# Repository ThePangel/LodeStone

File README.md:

# LodeStone

Don't lose your friends with this GPS LoRa P2P compass!

---

## The Idea 

### Where it came from
Just recently my district's fair started, and between all the crowds and the size of the fairgrounds It's pretty hard to find my friends, especially when we get separated, so with that and me playing a bunch of Minecraft this idea of a Mesh LoRa P2P compass came about.

The name is a reference to the lodestone block in Minecraft which lets you set custom compass targets.

---

### Features

- [ ] Compass like display pointing at the other nodes in the mesh network
- [ ] Top down map-like view of all nodes in the network
- [ ] Encrypted location data 
- [ ] Gesture based navigation using the gyroscope and accelerometer
- [ ] Short messages (Using some sort of keyboard using the gestures, or morse code)
- [ ] Heavily optimized battery life

---

### How would it work?
The device consists of 7 components:
- Seeed Studio XIAO ESP32 S3 Plus (As the brains of the device)
- Seeed Studio Lora32 SX1262 (For LoRa)
- Seeed Studio L76K GNSS Module (For GPS)
- GY-9250 BMP085 Module (For Accelerometer, Gyroscope and an actual compass)
- GC9A01 Round TFT screen 
- 503040 600mAh Battery
- Flexible antenna for the gps module (The standard ceramic one that comes with the module is far too bulky)

#### Connectivity 

The idea is that each node connects to each other individually or in groups, working simultaneously.

Pairing is done by a gesture password consisting of holds and taps, basically a morse code pin. You pair your devices using the same pin, then they handshake, share keys, and establish a connection.

Even if they are not paired (and if enabled), nodes retransmit incoming data packets to other users in the network to increase range.

#### Display 

The compass and map are drawn by taking GPS data from both nodes and the GY-9250 compass and accelerometer to calculate the direction the other node is at.

#### Battery

To optimize battery life and not saturate the airwaves, my system uses a Supply-demand approach. When the node (as a pendant or in the pocket) is still and facing away from the user, it is just listening for either location packets or a request packet. If it receives a location packet, it will update that node's location in memory and nothing else. If it receives a request packet, it will send its own location.

When the node is pulled up to be viewed, it will send a request packet to other nodes to update their location in memory, and a location packet so other nodes update it's location. It will do this at customizable intervals of time while it is being viewed. For signal integrity, the sending node must receive a confirmation packet back to ensure the transmission was successful. This workflow keeps battery usage to a minimum.

I still think it should ping at a set interval to guarante some type of connection, since maybe I can recieve my friends location, but he can't recieve my request so I knever know were he is
this could be also tied to speed using the accelerometer, this meaning, the more they move the more they send, if they are still it will default to some configurable interval

We could also tune transmition gain baised on distance, with some headroom of course

#### Interface

To maintain a compact formfactor, interaction with the node will be based on gestures, using the GY-9250 accelerometer and gyro.

Some of this gestures could be:
-   Tap/Double Tap
-   Shake
-   Tilt right/left/up/down

The menus would be similar to a smart watch.

#### Messaging

We can leverage our LoRa connection to send quick preconfigurable messages or write one at that moment using a gesture keyboard or morse code.

In the future I may develop an app to make this easier (tbh just use meshtashtic or meshcore atp), but this is intended for short notification like messages.

I would also like to add an SOS function that sends a signal to all nodes paired, or even if enabled on both ends, all nodes in the network, this will make the nodes flash red and highlight the SOS'ing node.

#### PCB 

The PCB is a simple 4 layer PCB that as compactly as possible houses all of the off the shelf components, making it very cheap and easy to assemble, the two outter planes hold traces and GND while the two inner layers are full ground pours, a bunch of vias connect the 4 GNDs to improve RF performance

#### 3D printed case

I will make a 3D printed case, as small and tight as possible for it to be portable and comfortable, of course anyone could design their own cases.

#### FOSS and modularity

I would like this project to be modular and community focused, so I encourage colaboration integrating for example:
-   Other ESP or microcontroller models
-   Other screens
-   Extra input components
-   Other IMU

etc.. all from the same modular firmware.

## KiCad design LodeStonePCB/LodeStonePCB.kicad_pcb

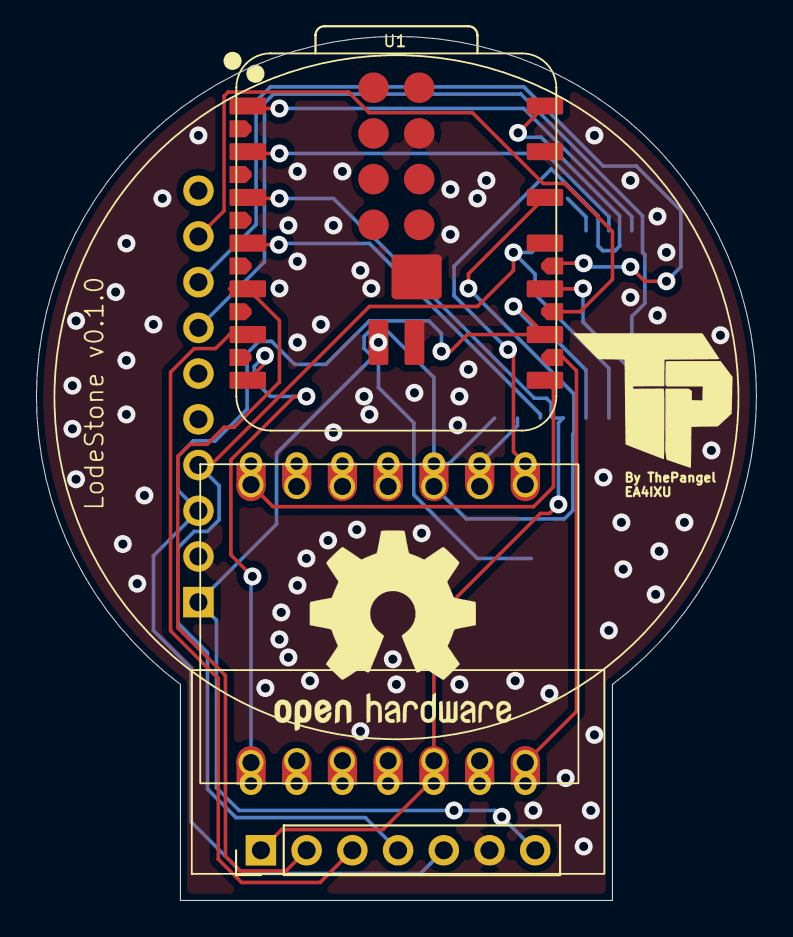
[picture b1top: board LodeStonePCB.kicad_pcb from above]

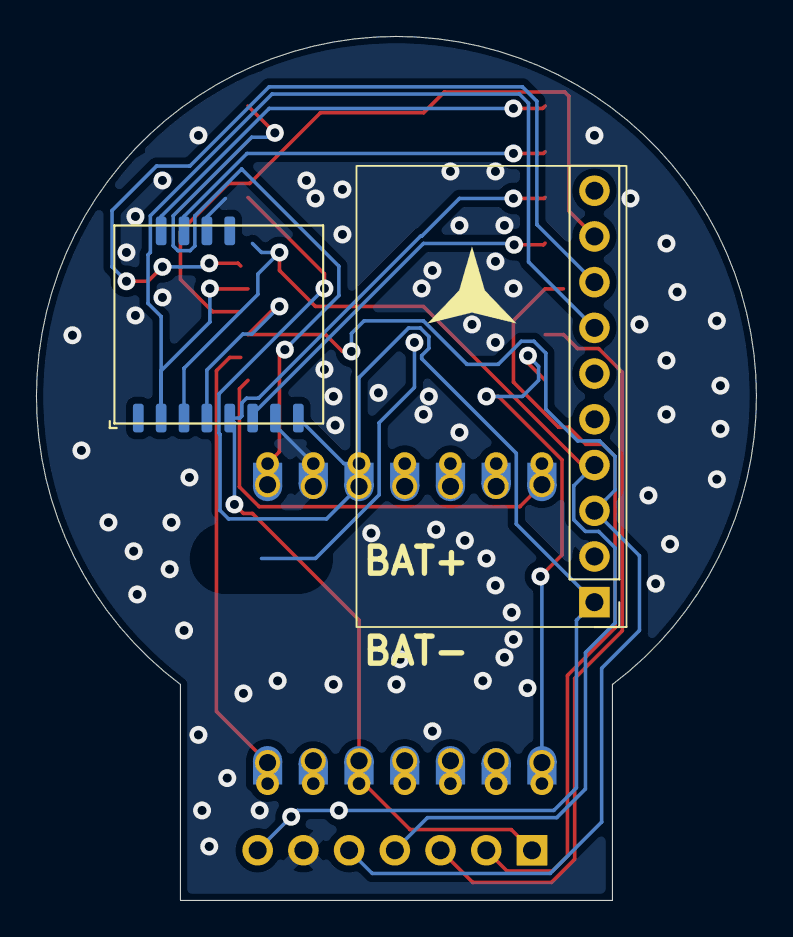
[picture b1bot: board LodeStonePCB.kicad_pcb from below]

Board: 4 copper layers, 40.0 x 48.0 mm, 5 parts (2 on the bottom side), 17 nets.

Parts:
GC9A01_Round_TFTscreen1: PinHeader_1x07_P2.54mm_Vertical
GY-9250_9Axis_IMU1: PinHeader_1x10_P2.54mm_Vertical
L76K_GNSS_Module1: XIAO-14P-Add-On
U1: XIAO-ESP32-S3-Plus-SMD
U2: LoRa; Wio-SX1262 PCB Package

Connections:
+3V3: GC9A01_Round_TFTscreen1.7 (VCC), GY-9250_9Axis_IMU1.1 (VCC), L76K_GNSS_Module1.3 (3V3), U1.12 (3V3), U2.8 (VCC)
+5V: L76K_GNSS_Module1.1 (5V), U1.14 (VBUS)
/CS_IMU: GY-9250_9Axis_IMU1.9 (NCS), U1.22 (GPIO12_DVP_Y7_SPI_MISO1)
/CS_LoRa: U1.4 (GPIO4_A3_D3), U2.6 (NSS)
/CS_SCREEN: GC9A01_Round_TFTscreen1.2 (CS), U1.5 (GPIO5_A4_D4_SDA)
/DC_SCREEN: GC9A01_Round_TFTscreen1.3 (DC), U1.6 (GPIO6_A5_D5_SCL)
/INT_IMU: GY-9250_9Axis_IMU1.8 (INT), U1.23 (GPIO13_DVP_PCLK_SPI_SCK1)
/LoRa_BUSY: U1.2 (GPIO2_A1_D1), U2.11 (BUSY)
/LoRa_DI01: U1.1 (GPIO1_A0_D0), U2.12 (DIO1)
/MISO: GY-9250_9Axis_IMU1.7 (ADO), U1.10 (GPIO8_A9_D9_MISO), U2.2 (MISO)
/MOSI: GC9A01_Round_TFTscreen1.4 (SDA), GY-9250_9Axis_IMU1.4 (SDA), U1.11 (GPIO9_A10_D10_MOSI), U2.3 (MOSI)
/RST: GC9A01_Round_TFTscreen1.1 (RST), L76K_GNSS_Module1.12 (RST), U1.3 (GPIO3_A2_D2), U2.5 (RST)
/SCK: GC9A01_Round_TFTscreen1.5 (SCL), GY-9250_9Axis_IMU1.3 (SCL), U1.9 (GPIO7_A8_D8_SCK), U2.4 (SCK)
/UART_RX: L76K_GNSS_Module1.7 (TX), U1.8 (GPIO44_D7_RX)
/UART_TX: L76K_GNSS_Module1.8 (RX), U1.7 (GPIO43_D6_TX)
/WUP_GNSS: L76K_GNSS_Module1.14 (WUP), U1.21 (GPIO11_DVP_Y8_SPI_MOSI1)
GND: GC9A01_Round_TFTscreen1.6 (GND), GY-9250_9Axis_IMU1.2 (GND), L76K_GNSS_Module1.2 (GND), U1.13 (GND), U1.27 (GND1), U1.33 (GND2), U1.34 (PAD), U2.7 (GND1), U2.10 (GND2)

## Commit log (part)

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2026-06-01 Set project basis
2026-06-02 Expanded goals
2026-06-02 Didn't save before pushing lmao
2026-06-02 Corrections in README
2026-06-07 Started PCB
2026-06-07 Finished pcb
2026-06-07 Images to readme
